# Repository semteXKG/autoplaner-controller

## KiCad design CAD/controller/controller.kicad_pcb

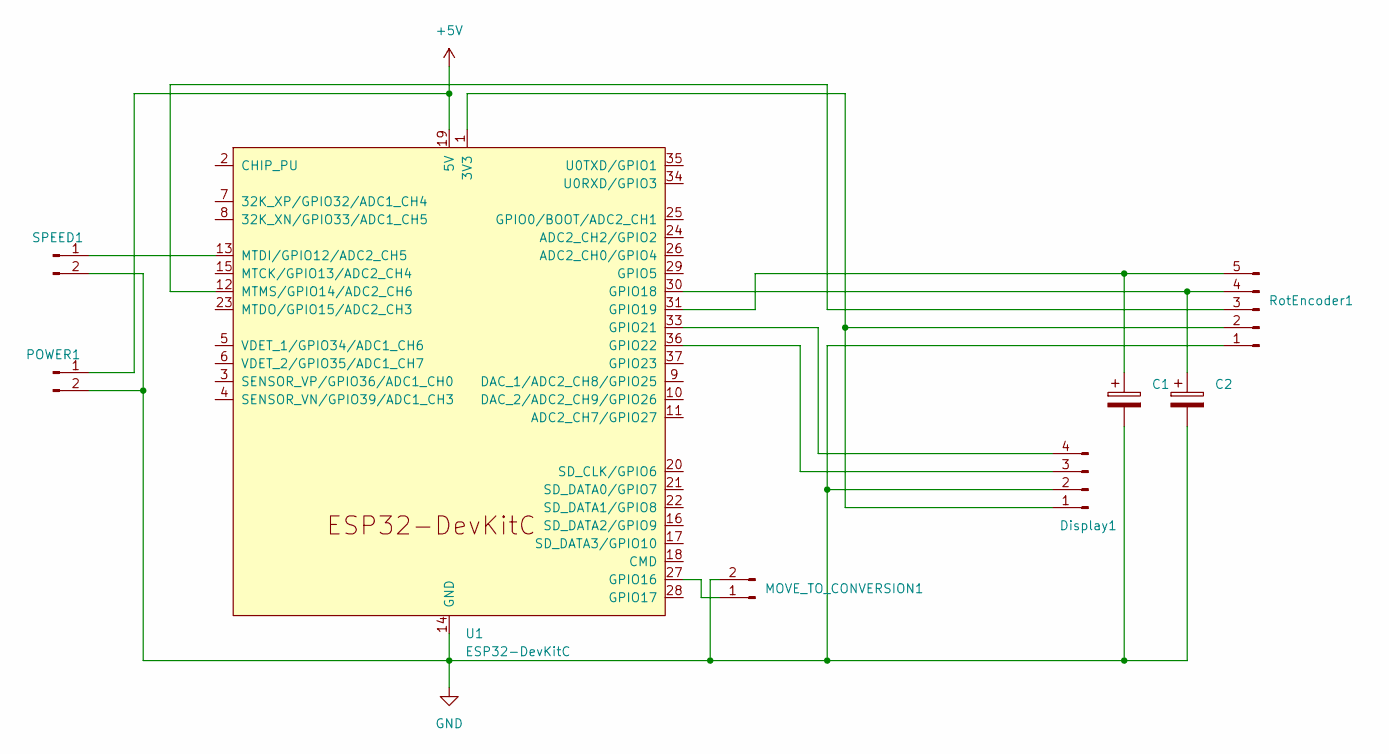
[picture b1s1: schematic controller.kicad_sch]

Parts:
C1, C2: 0.1uF; CP_Radial_D5.0mm_P2.00mm
Display1: Conn_01x04_Pin; JST_XH_B4B-XH-A_1x04_P2.50mm_Vertical
MOVE_TO_CONVERSION1: Conn_01x02_Pin; JST_XH_B2B-XH-A_1x02_P2.50mm_Vertical
POWER1: Conn_01x02_Pin; JST_XH_B2B-XH-A_1x02_P2.50mm_Vertical
RotEncoder1: Conn_01x05_Pin; JST_XH_B5B-XH-A_1x05_P2.50mm_Vertical
SPEED1: Conn_01x02_Pin; JST_XH_B2B-XH-A_1x02_P2.50mm_Vertical
U1: ESP32-DevKitC

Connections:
+5V: POWER1.1, U1.19 (5V)
GND: C1.2, C2.2, Display1.2, MOVE_TO_CONVERSION1.2, POWER1.2, RotEncoder1.1, SPEED1.2, U1.14 (GND), U1.32 (GND), U1.38 (GND)
unnamed: Display1.1, RotEncoder1.2, U1.1 (3V3)
unnamed: Display1.3, U1.36 (GPIO22)
unnamed: Display1.4, U1.33 (GPIO21)
unnamed: MOVE_TO_CONVERSION1.1, U1.27 (GPIO16)
unnamed: RotEncoder1.3, U1.12 (MTMS/GPIO14/ADC2_CH6)
unnamed: C2.1, RotEncoder1.4, U1.30 (GPIO18)
unnamed: C1.1, RotEncoder1.5, U1.31 (GPIO19)
unnamed: SPEED1.1, U1.13 (MTDI/GPIO12/ADC2_CH5)

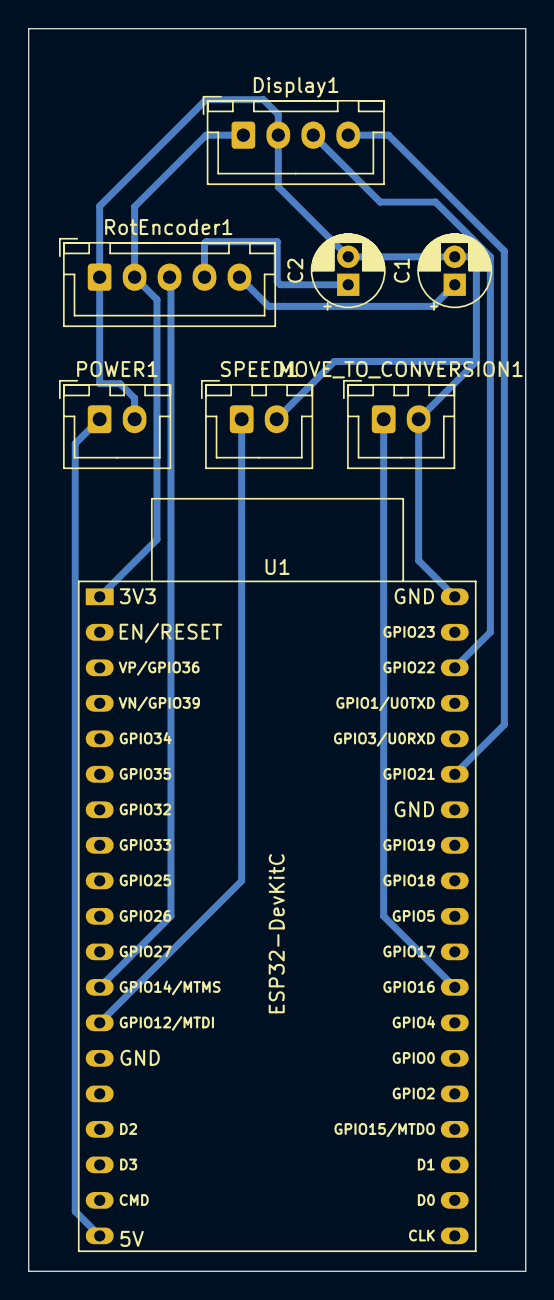
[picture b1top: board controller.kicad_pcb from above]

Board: 2 copper layers, 35.6 x 88.9 mm, 8 parts (0 on the bottom side), 10 nets.

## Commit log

2024-01-04 adding sync mechanism
2024-01-04 removed unused classes
2024-01-04 Fixing rotator
2024-01-05 adding new state
2024-01-05 updating data structure in dynamic allocation
2024-01-05 switching back to real settings
2024-01-05 NVstuff is now all handled on driver
2024-01-06 fixing button issues
2024-01-06 fixed rotation when using fractions
2024-01-06 minor fixes
2024-01-06 adding kicad model
2024-01-07 updating drawings
2024-01-15 Updated PCB
